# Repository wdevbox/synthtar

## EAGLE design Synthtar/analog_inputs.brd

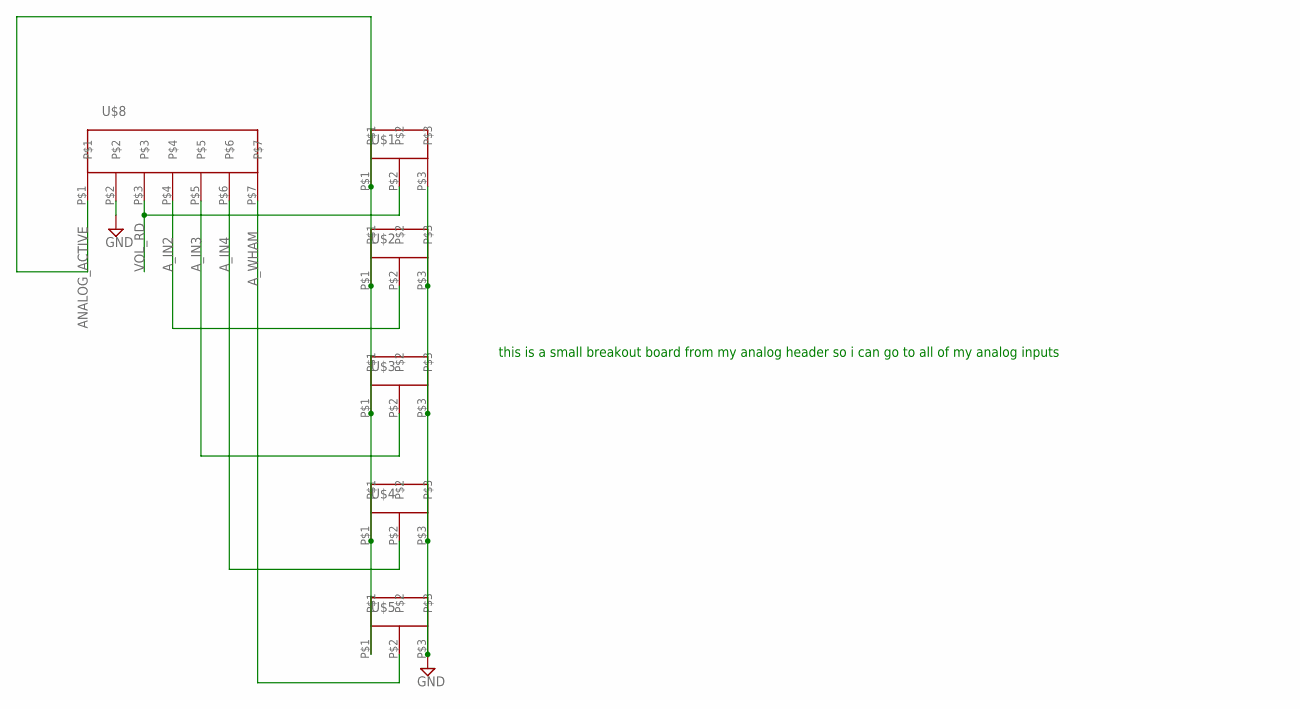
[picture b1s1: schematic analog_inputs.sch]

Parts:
U$1, U$2, U$3, U$4, U$5: 3-PIN-HEADER
U$8: 7-PIN-HEADER

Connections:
ANALOG_ACTIVE: U$1.P$1, U$2.P$1, U$3.P$1, U$4.P$1, U$5.P$1, U$8.P$1
A_IN2: U$2.P$2, U$8.P$4
A_IN3: U$3.P$2, U$8.P$5
A_IN4: U$4.P$2, U$8.P$6
A_WHAM: U$5.P$2, U$8.P$7
GND: U$1.P$3, U$2.P$3, U$3.P$3, U$4.P$3, U$5.P$3, U$8.P$2
VOL_RD: U$1.P$2, U$8.P$3

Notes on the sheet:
this is a small breakout board from my analog header so i can go to all of my analog inputs

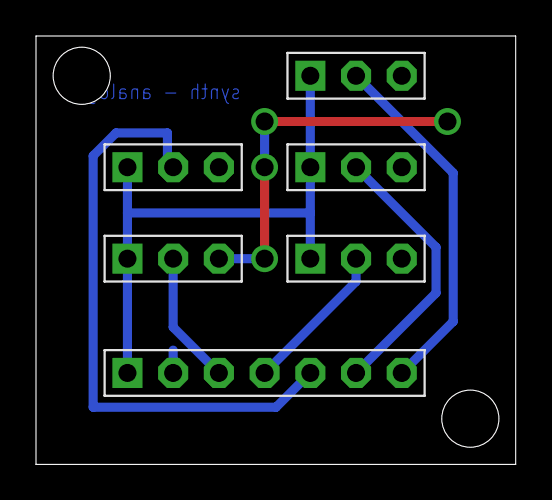
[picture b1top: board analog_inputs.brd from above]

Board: 2 copper layers, 26.7 x 23.8 mm, 6 parts (0 on the bottom side), 7 nets.

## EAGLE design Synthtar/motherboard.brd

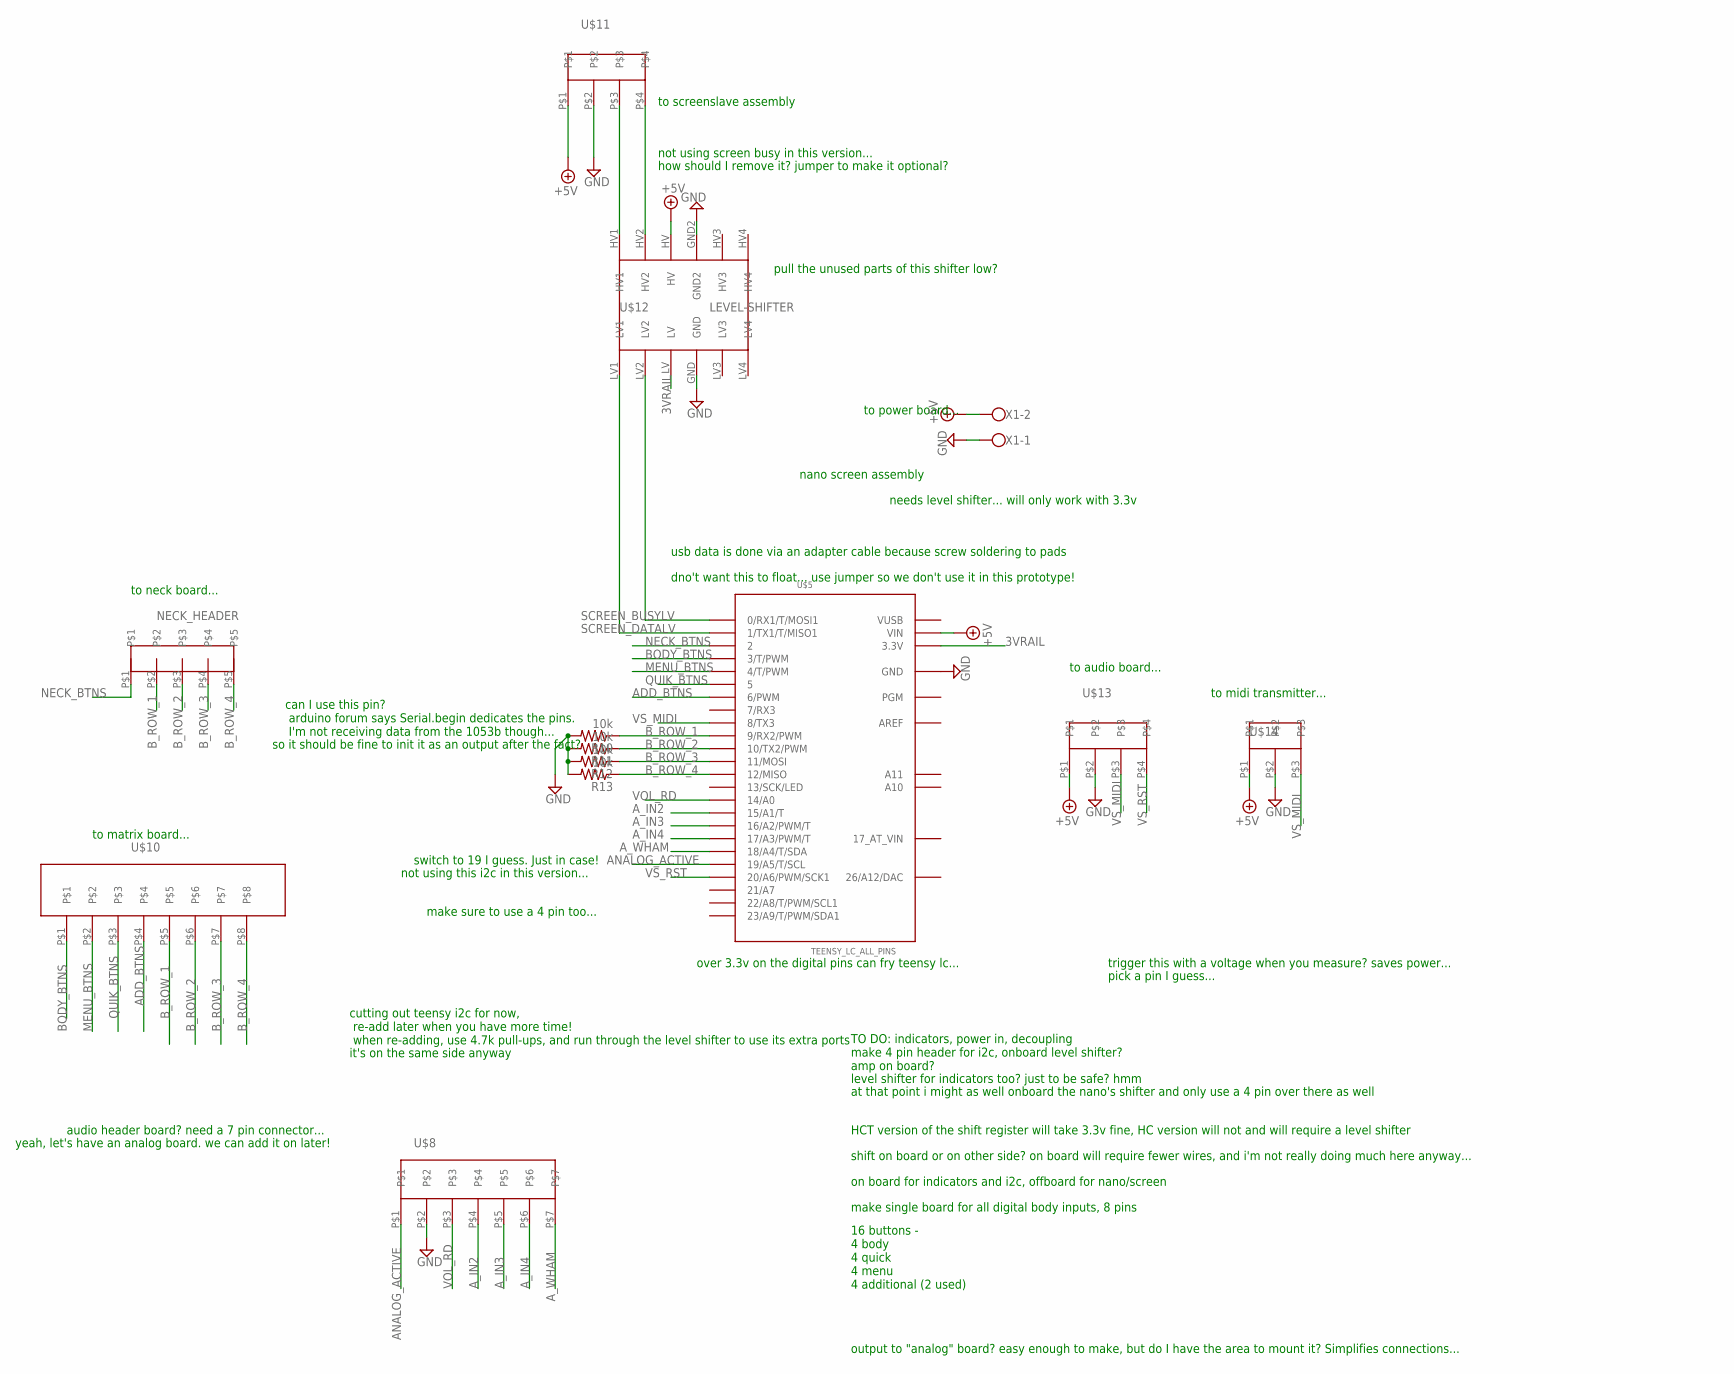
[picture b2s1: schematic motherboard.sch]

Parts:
NECK_HEADER: 5-PIN-HEADER
R10, R11, R12, R13: 10k; 0204/7
U$5: TEENSY_LC_ALL_PINS; TEENSY_3.0-3.2&LC_ALL_PINS
U$8: 7-PIN-HEADER
U$10: 8-PIN-HEADER
U$11, U$13: 4-PIN-HEADER
U$12: LEVEL-SHIFTER
U$14: 3-PIN-HEADER
X1: W237-102

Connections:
3VRAIL: U$5.3.3V, U$5.3.3V1 (3.3V), U$12.LV
26/A12/DAC: U$5.RESET/DAC (26/A12/DAC)
+5V: U$5.VIN, U$11.P$1, U$12.HV, U$13.P$1, U$14.P$1, X1.2
ADD_BTNS: U$5.6 (6/PWM), U$10.P$4
ANALOG_ACTIVE: U$5.19/A5 (19/A5/T/SCL), U$8.P$1
AREF: U$5.AREF
A_IN2: U$5.15/A1 (15/A1/T), U$8.P$4
A_IN3: U$5.16/A2 (16/A2/PWM/T), U$8.P$5
A_IN4: U$5.17/A3 (17/A3/PWM/T), U$8.P$6
A_WHAM: U$5.18/A4 (18/A4/T/SDA), U$8.P$7
BODY_BTNS: U$5.3 (3/T/PWM), U$10.P$1
B_ROW_1: NECK_HEADER.P$2, R10.1, U$5.9 (9/RX2/PWM), U$10.P$5
B_ROW_2: NECK_HEADER.P$3, R11.1, U$5.10 (10/TX2/PWM), U$10.P$6
B_ROW_3: NECK_HEADER.P$4, R12.1, U$5.11 (11/MOSI), U$10.P$7
B_ROW_4: NECK_HEADER.P$5, R13.1, U$5.12 (12/MISO), U$10.P$8
GND: R10.2, R11.2, R12.2, R13.2, U$5.AGND (GND), U$5.GND, U$5.GND1 (GND), U$8.P$2, U$11.P$2, U$12.GND, U$12.GND2, U$13.P$2, U$14.P$2, X1.1
MENU_BTNS: U$5.4 (4/T/PWM), U$10.P$2
unnamed: U$11.P$3, U$12.HV1
unnamed: U$11.P$4, U$12.HV2
NECK_BTNS: NECK_HEADER.P$1, U$5.2
QUIK_BTNS: U$5.5, U$10.P$3
SCREEN_BUSYLV: U$5.0 (0/RX1/T/MOSI1), U$12.LV2
SCREEN_DATALV: U$5.1 (1/TX1/T/MISO1), U$12.LV1
VOL_RD: U$5.14/A0, U$8.P$3
VS_MIDI: U$5.8 (8/TX3), U$13.P$3, U$14.P$3
VS_RST: U$5.20/A6 (20/A6/PWM/SCK1), U$13.P$4
VUSB: U$5.VUSB

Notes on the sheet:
over 3.3v on the digital pins can fry teensy lc...
nano screen assembly
TO DO: indicators, power in, decoupling make 4 pin header for i2c, onboard level shifter? amp on board?
level shifter for indicators too? just to be safe? hmm
at that point i might as well onboard the nano's shifter and only use a 4 pin over there as well
HCT version of the shift register will take 3.3v fine, HC version will not and will require a level shifter
shift on board or on other side? on board will require fewer wires, and i'm not really doing much here anyway...
needs level shifter... will only work with 3.3v
on board for indicators and i2c, offboard for nano/screen
make single board for all digital body inputs, 8 pins
16 buttons - 4 body 4 quick 4 menu 4 additional (2 used)
output to "analog" board? easy enough to make, but do I have the area to mount it? Simplifies connections...
to matrix board...
to neck board...
to power board...
to audio board...
to midi transmitter...
usb data is done via an adapter cable because screw soldering to pads
to screenslave assembly
not using screen busy in this version...
how should I remove it? jumper to make it optional?
pull the unused parts of this shifter low?
dno't want this to float... use jumper so we don't use it in this prototype!
not using this i2c in this version...
audio header board? need a 7 pin connector...
yeah, let's have an analog board. we can add it on later!
trigger this with a voltage when you measure? saves power...
pick a pin I guess...
can I use this pin? arduino forum says Serial.begin dedicates the pins. I'm not receiving data from the 1053b though...
so it should be fine to init it as an output after the fact?
switch to 19 I guess. Just in case!
cutting out teensy i2c for now, re-add later when you have more time! when re-adding, use 4.7k pull-ups, and run through the level shifter to use its extra ports
it's on the same side anyway
make sure to use a 4 pin too...

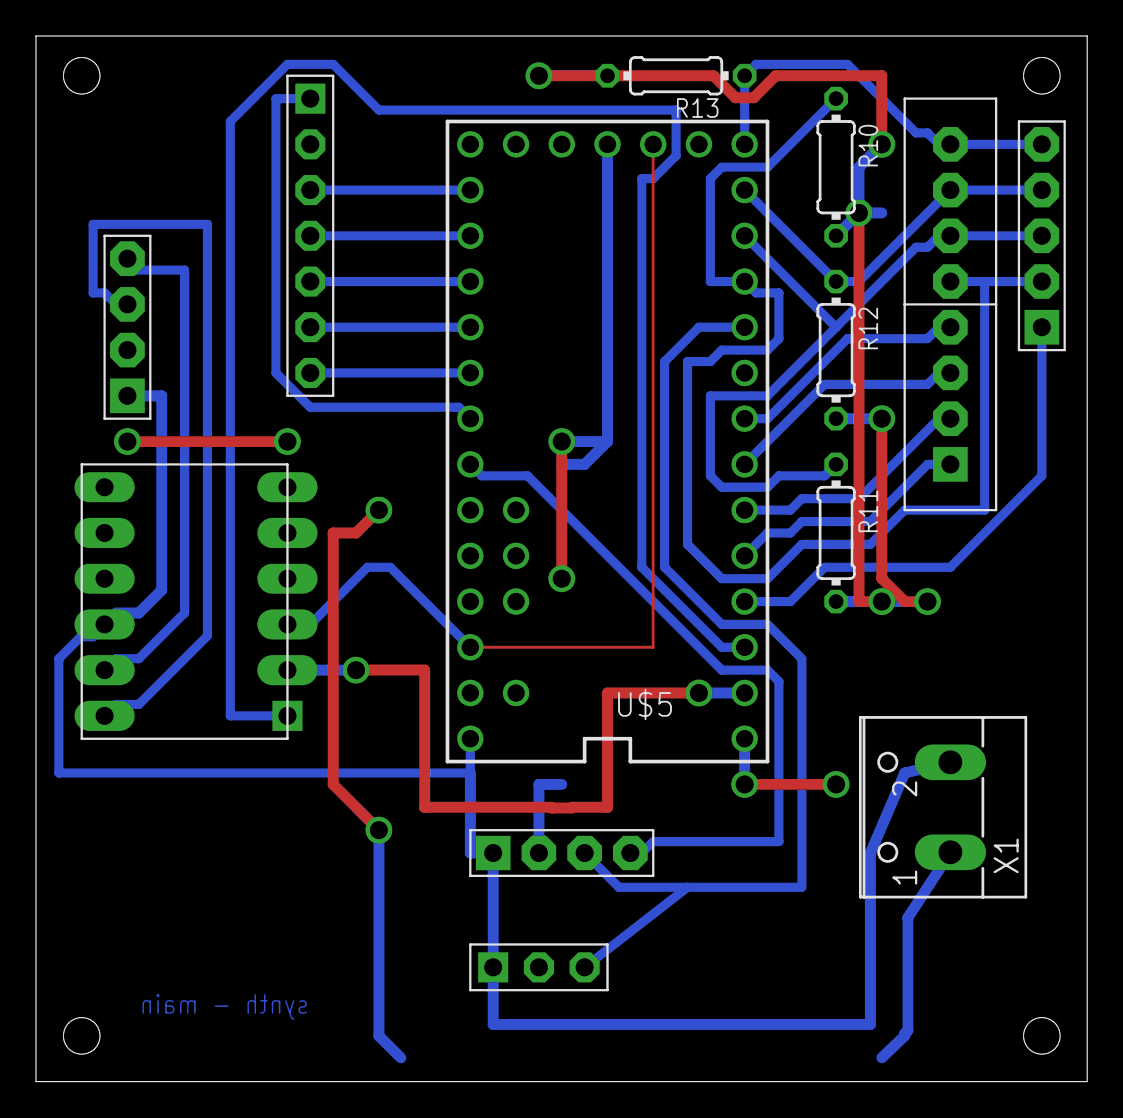
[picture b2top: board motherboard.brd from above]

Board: 2 copper layers, 58.4 x 58.1 mm, 13 parts (0 on the bottom side), 24 nets.

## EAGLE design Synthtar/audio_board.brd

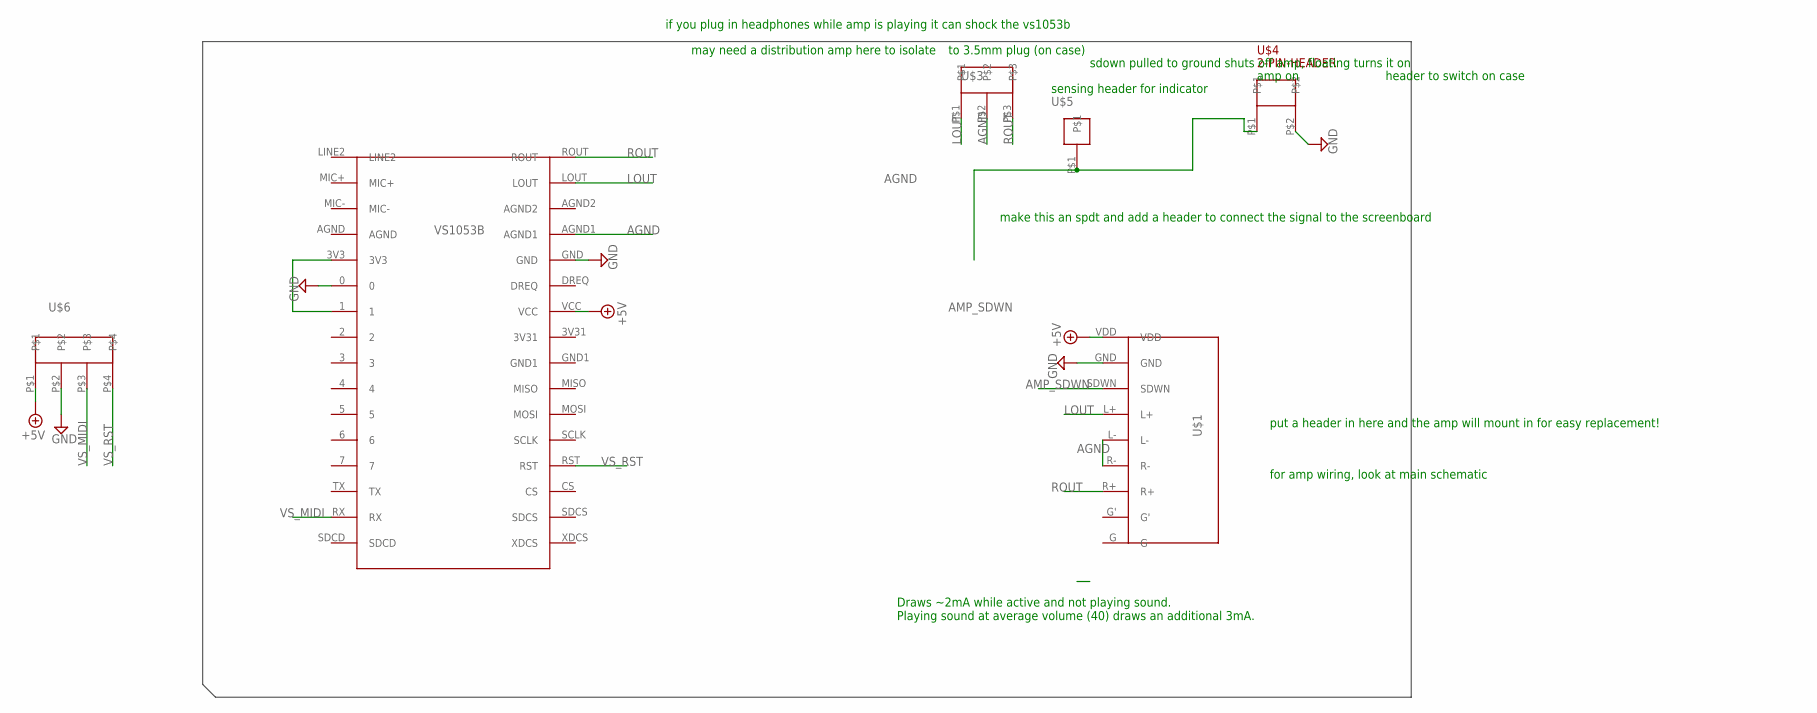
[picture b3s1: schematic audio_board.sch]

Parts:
U$1: AUDIOAMP
U$3: 3-PIN-HEADER
U$4: 2-PIN-HEADER
U$5: 1-PIN-HEADER
U$6: 4-PIN-HEADER
VS1053B: VS1053B

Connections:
+5V: U$1.VDD, U$6.P$1, VS1053B.VCC
AGND: U$1.L-, U$1.R-, U$3.P$2, VS1053B.AGND1
AMP_SDWN: U$1.SDWN, U$4.P$1, U$5.P$1
GND: U$1.GND, U$4.P$2, U$6.P$2, VS1053B.0, VS1053B.GND
LOUT: U$1.L+, U$3.P$1, VS1053B.LOUT
unnamed: VS1053B.1, VS1053B.3V3
ROUT: U$1.R+, U$3.P$3, VS1053B.ROUT
VS_MIDI: U$6.P$3, VS1053B.RX
VS_RST: U$6.P$4, VS1053B.RST

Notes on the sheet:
amp on
sdown pulled to ground shuts off amp, floating turns it on
Draws ~2mA while active and not playing sound. Playing sound at average volume (40) draws an additional 3mA.
may need a distribution amp here to isolate
if you plug in headphones while amp is playing it can shock the vs1053b
make this an spdt and add a header to connect the signal to the screenboard
to 3.5mm plug (on case)
header to switch on case
sensing header for indicator
put a header in here and the amp will mount in for easy replacement!
for amp wiring, look at main schematic

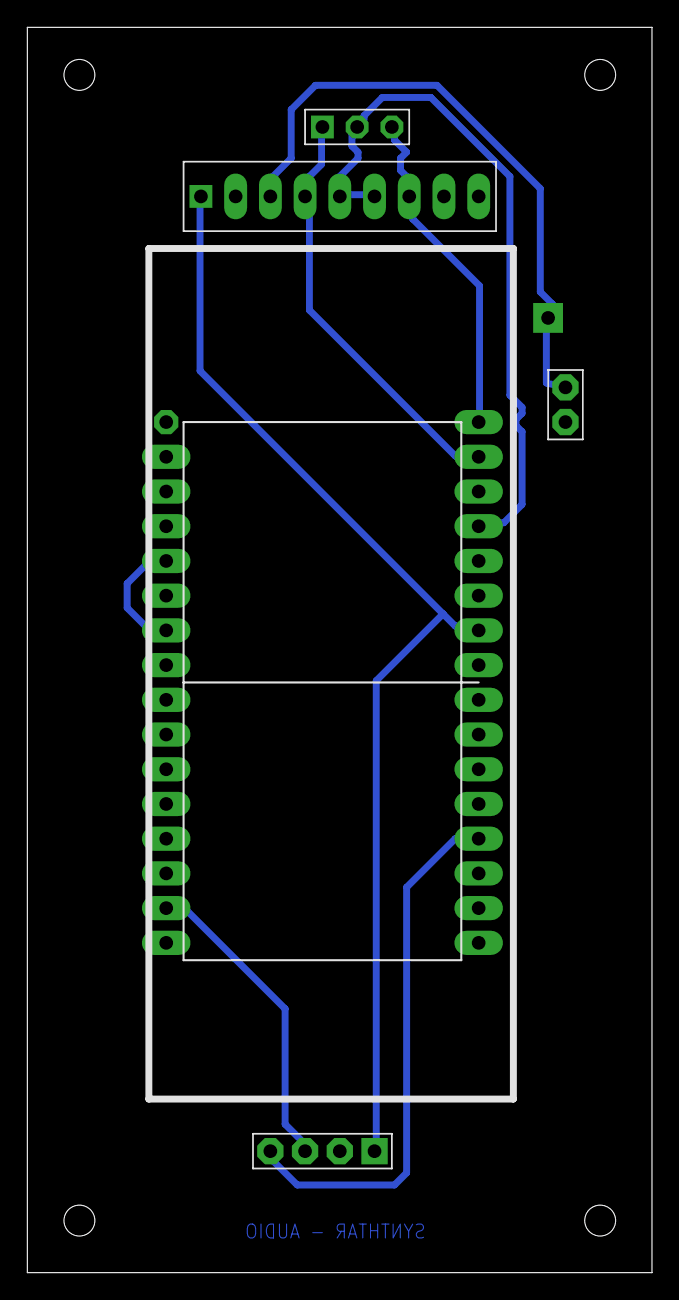
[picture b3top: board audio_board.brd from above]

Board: 2 copper layers, 45.7 x 91.1 mm, 6 parts (0 on the bottom side), 9 nets.

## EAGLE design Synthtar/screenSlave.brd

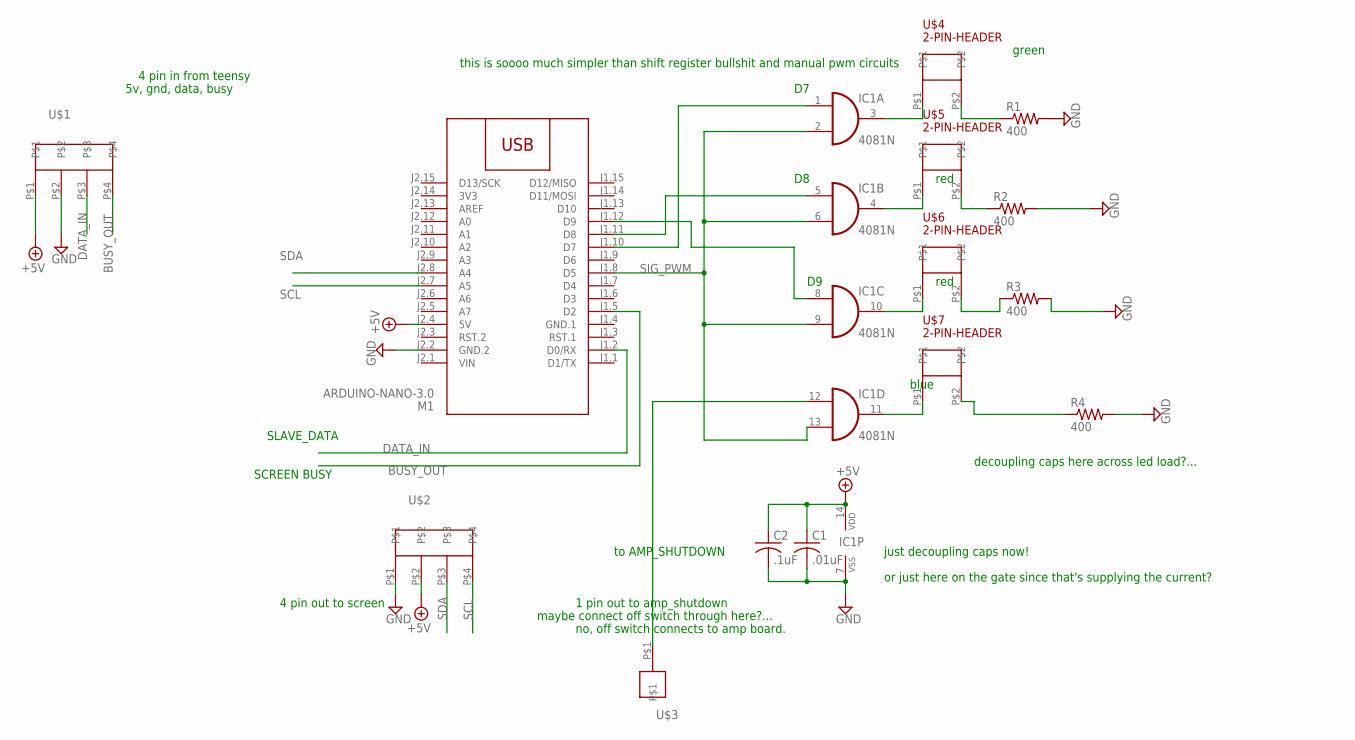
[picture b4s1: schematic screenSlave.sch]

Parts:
C1: .01uF; C025-024X044
C2: .1uF; C025-024X044
IC1: 4081N; DIL14
M1: ARDUINO-NANO-3.0
R1, R2, R3, R4: 400; 0204/7
U$1, U$2: 4-PIN-HEADER
U$3: 1-PIN-HEADER
U$4, U$5, U$6, U$7: 2-PIN-HEADER

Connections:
3V3: M1.J2.14 (3V3)
+5V: C1.1, C2.1, IC1.14 (VDD), M1.J2.4 (5V), U$1.P$1, U$2.P$2
BUSY_OUT: M1.J1.5 (D2), U$1.P$4
DATA_IN: M1.J1.2 (D0/RX), U$1.P$3
GND: C1.2, C2.2, IC1.7 (VSS), M1.J2.2 (GND.2), R1.2, R2.2, R3.2, R4.2, U$1.P$2, U$2.P$1
GND.1: M1.J1.4 (GND.1)
unnamed: IC1.12 (I0), U$3.P$1
unnamed: IC1.11 (O), U$7.P$1
unnamed: IC1.3 (O), U$4.P$1
unnamed: R1.1, U$4.P$2
unnamed: IC1.4 (O), U$5.P$1
unnamed: IC1.10 (O), U$6.P$1
unnamed: R3.1, U$6.P$2
unnamed: IC1.1 (I0), M1.J1.10 (D7)
unnamed: R2.1, U$5.P$2
unnamed: IC1.5 (I0), M1.J1.11 (D8)
unnamed: IC1.8 (I0), M1.J1.12 (D9)
unnamed: R4.1, U$7.P$2
SCL: M1.J2.7 (A5), U$2.P$4
SDA: M1.J2.8 (A4), U$2.P$3
SIG_PWM: IC1.2 (I1), IC1.6 (I1), IC1.9 (I1), IC1.13 (I1), M1.J1.8 (D5)
VIN: M1.J2.1 (VIN)

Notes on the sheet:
blue
red
green
to AMP_SHUTDOWN
SLAVE_DATA
SCREEN BUSY
4 pin in from teensy
4 pin out to screen
1 pin out to amp_shutdown
5v, gnd, data, busy
maybe connect off switch through here?...
this is soooo much simpler than shift register bullshit and manual pwm circuits
just decoupling caps now!
decoupling caps here across led load?...
or just here on the gate since that's supplying the current?
no, off switch connects to amp board.

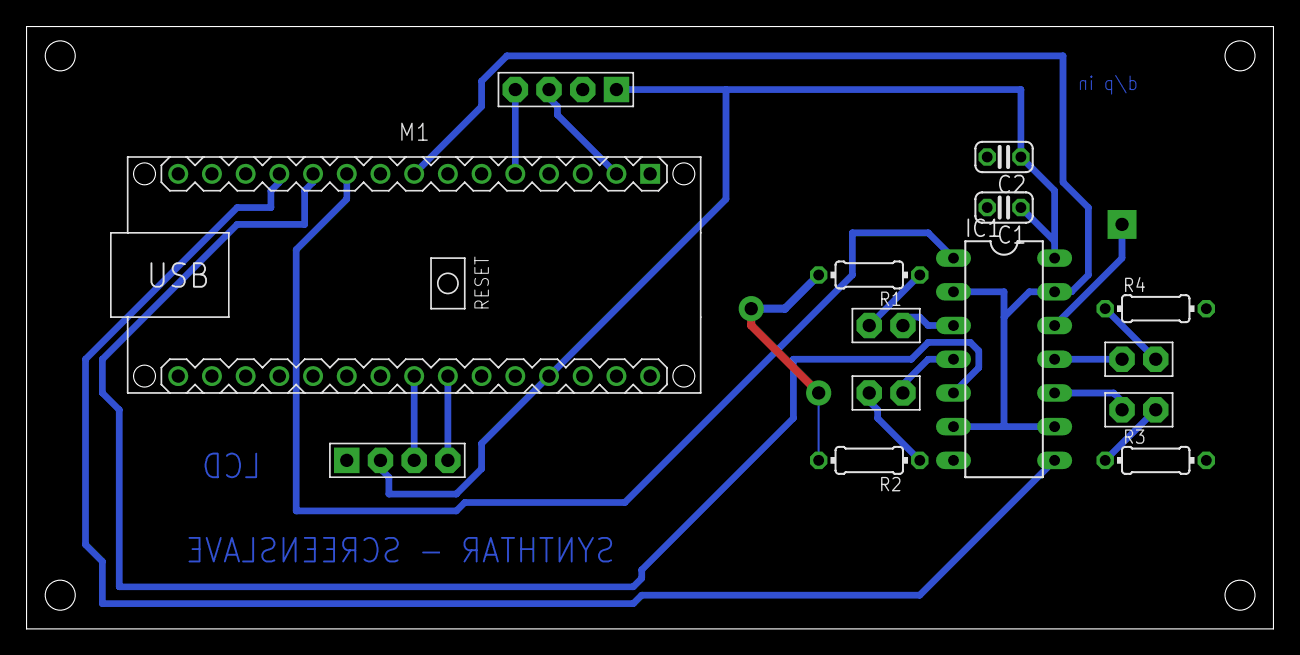
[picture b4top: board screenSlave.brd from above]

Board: 2 copper layers, 94.0 x 45.4 mm, 15 parts (0 on the bottom side), 19 nets.

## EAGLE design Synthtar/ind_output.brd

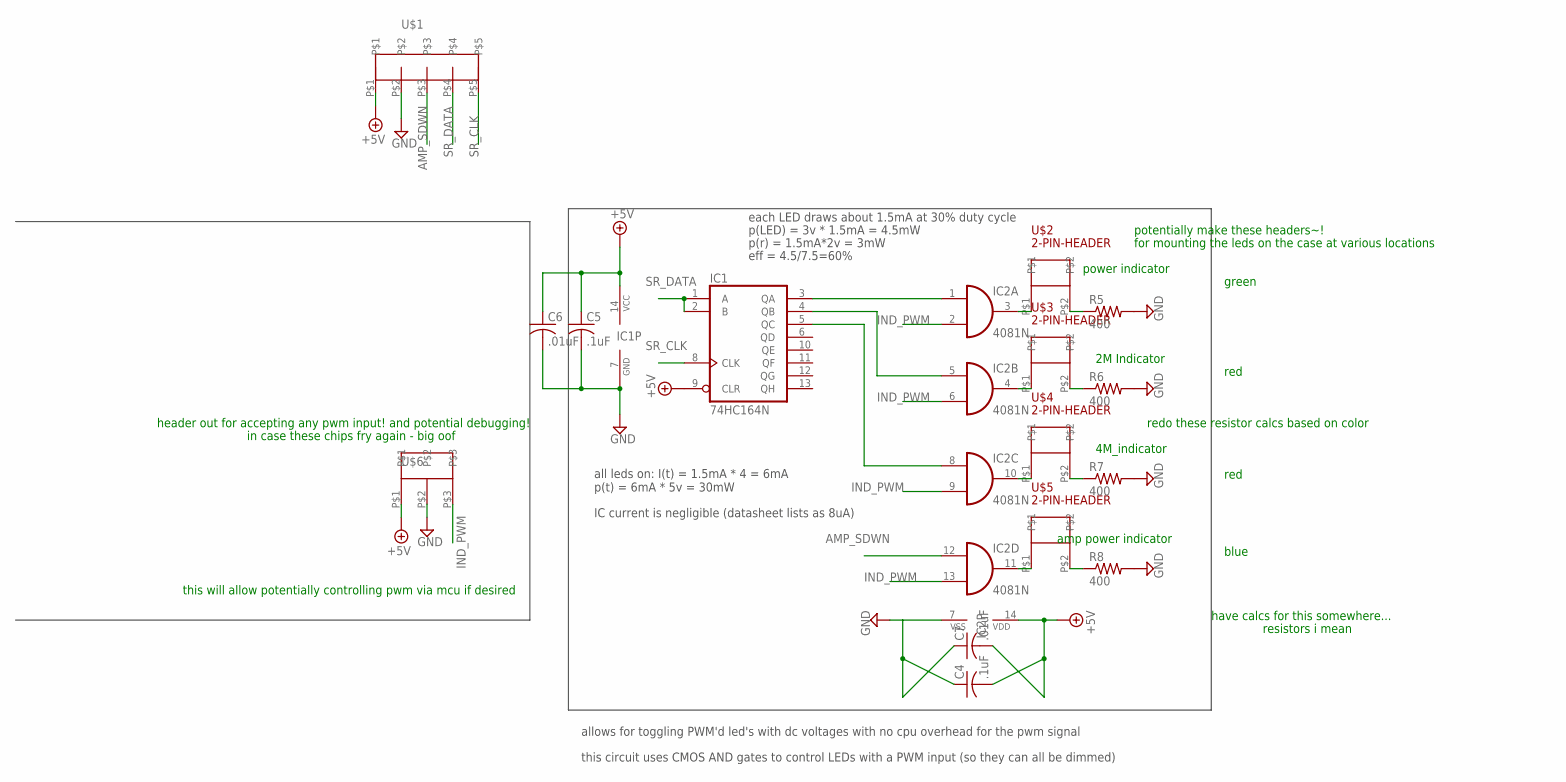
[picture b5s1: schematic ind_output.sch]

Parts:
C4, C5: .1uF; C025-030X050
C6, C7: .01uF; C025-030X050
IC1: 74HC164N; DIL14
IC2: 4081N; DIL14
R5, R6, R7, R8: 400; 0204/7
U$1: 5-PIN-HEADER
U$2, U$3, U$4, U$5: 2-PIN-HEADER
U$6: 3-PIN-HEADER

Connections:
+5V: C4.2, C5.1, C6.1, C7.2, IC1.9 (CLR), IC1.14 (VCC), IC2.14 (VDD), U$1.P$1, U$6.P$1
AMP_SDWN: IC2.12 (I0), U$1.P$3
GND: C4.1, C5.2, C6.2, C7.1, IC1.7 (GND), IC2.7 (VSS), R5.2, R6.2, R7.2, R8.2, U$1.P$2, U$6.P$2
IND_PWM: IC2.2 (I1), IC2.6 (I1), IC2.9 (I1), IC2.13 (I1), U$6.P$3
unnamed: IC1.3 (QA), IC2.1 (I0)
unnamed: IC1.4 (QB), IC2.5 (I0)
unnamed: IC2.3 (O), U$2.P$1
unnamed: IC1.5 (QC), IC2.8 (I0)
unnamed: R5.1, U$2.P$2
unnamed: IC2.4 (O), U$3.P$1
unnamed: R6.1, U$3.P$2
unnamed: IC2.10 (O), U$4.P$1
unnamed: R7.1, U$4.P$2
unnamed: IC2.11 (O), U$5.P$1
unnamed: R8.1, U$5.P$2
SR_CLK: IC1.8 (CLK), U$1.P$5
SR_DATA: IC1.1 (A), IC1.2 (B), U$1.P$4

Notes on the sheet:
amp power indicator
2M Indicator
4M_indicator
power indicator
this circuit uses CMOS AND gates to control LEDs with a PWM input (so they can all be dimmed)
allows for toggling PWM'd led's with dc voltages with no cpu overhead for the pwm signal
each LED draws about 1.5mA at 30% duty cycle
p(LED) = 3v * 1.5mA = 4.5mW
p(r) = 1.5mA*2v = 3mW
eff = 4.5/7.5=60%
all leds on: I(t) = 1.5mA * 4 = 6mA p(t) = 6mA * 5v = 30mW
IC current is negligible (datasheet lists as 8uA)
potentially make these headers~!
for mounting the leds on the case at various locations
redo these resistor calcs based on color
green
blue
red
have calcs for this somewhere...
resistors i mean
header out for accepting any pwm input! and potential debugging!
in case these chips fry again - big oof
this will allow potentially controlling pwm via mcu if desired

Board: 2 copper layers, 16 parts (0 on the bottom side), 17 nets, no tracks yet.

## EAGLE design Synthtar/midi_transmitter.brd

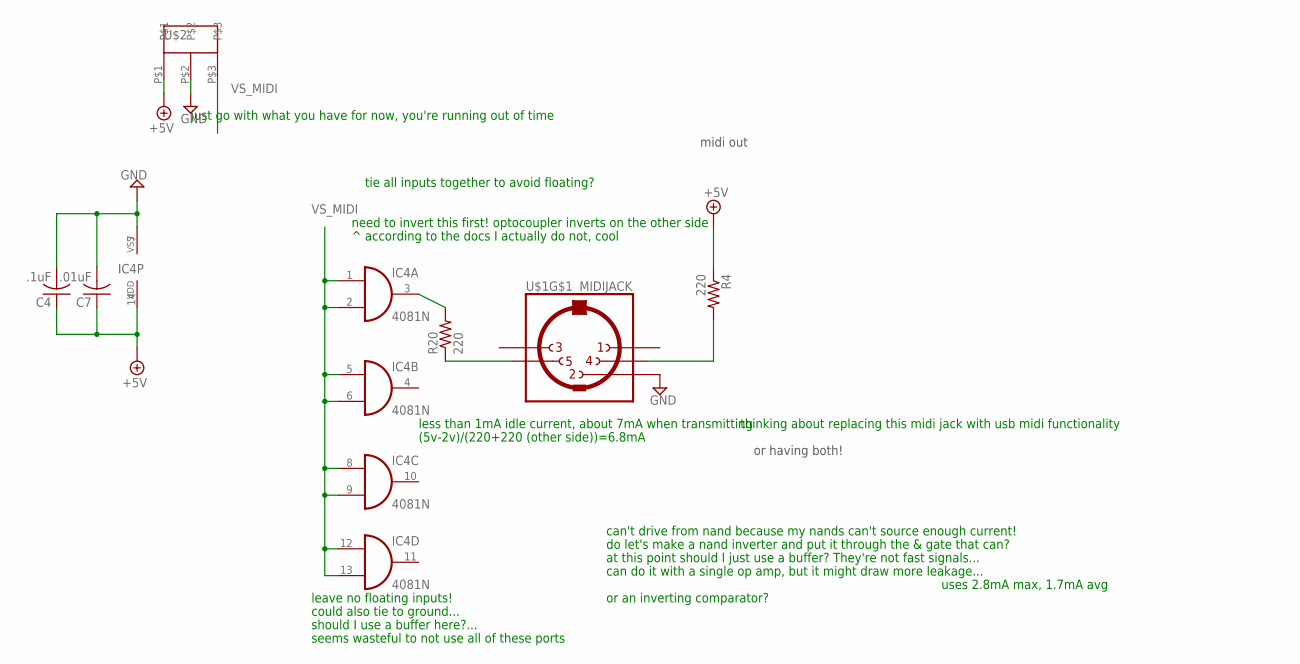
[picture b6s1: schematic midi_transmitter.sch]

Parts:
C4: .1uF; C025-030X050
C7: .01uF; C025-030X050
IC4: 4081N; DIL14
R4, R20: 220; 0204/7
U$1: MIDIJACK; CP-2350
U$2: 3-PIN-HEADER

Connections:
+5V: C4.1, C7.1, IC4.14 (VDD), R4.1, U$2.P$1
GND: C4.2, C7.2, IC4.7 (VSS), U$1.2, U$2.P$2
unnamed: IC4.3 (O), R20.2
unnamed: R4.2, U$1.4
unnamed: R20.1, U$1.5
VS_MIDI: IC4.1 (I0), IC4.2 (I1), IC4.5 (I0), IC4.6 (I1), IC4.8 (I0), IC4.9 (I1), IC4.12 (I0), IC4.13 (I1), U$2.P$3

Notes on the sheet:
midi out
thinking about replacing this midi jack with usb midi functionality
or having both!
need to invert this first! optocoupler inverts on the other side
tie all inputs together to avoid floating?
can't drive from nand because my nands can't source enough current!
do let's make a nand inverter and put it through the & gate that can?
at this point should I just use a buffer? They're not fast signals...
can do it with a single op amp, but it might draw more leakage...
or an inverting comparator?
uses 2.8mA max, 1.7mA avg
just go with what you have for now, you're running out of time
^ according to the docs I actually do not, cool
less than 1mA idle current, about 7mA when transmitting
(5v-2v)/(220+220 (other side))=6.8mA
leave no floating inputs!
could also tie to ground...
should I use a buffer here?...
seems wasteful to not use all of these ports

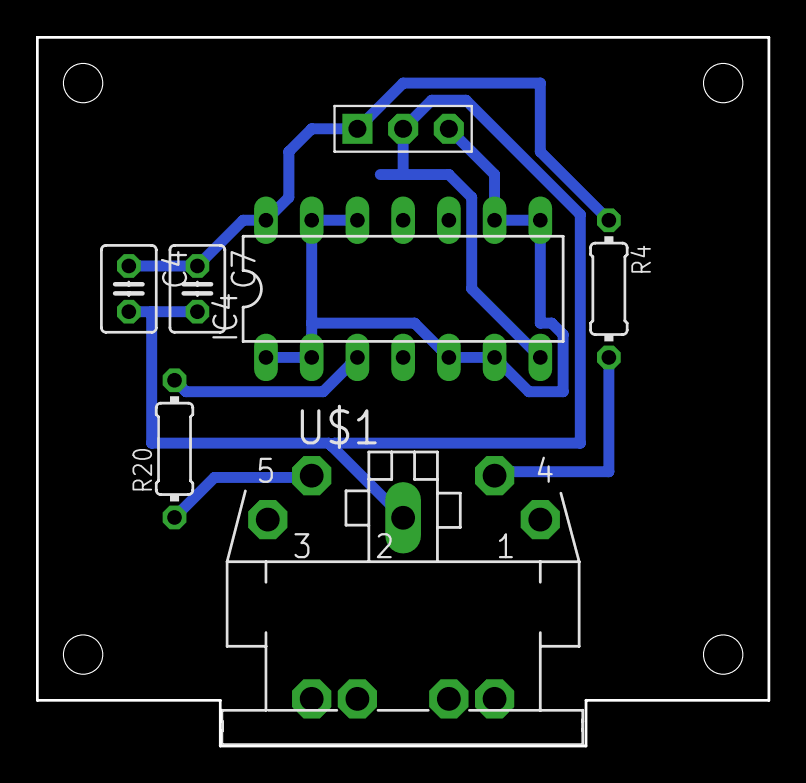
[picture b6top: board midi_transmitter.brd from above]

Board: 2 copper layers, 40.6 x 39.4 mm, 7 parts (0 on the bottom side), 6 nets.

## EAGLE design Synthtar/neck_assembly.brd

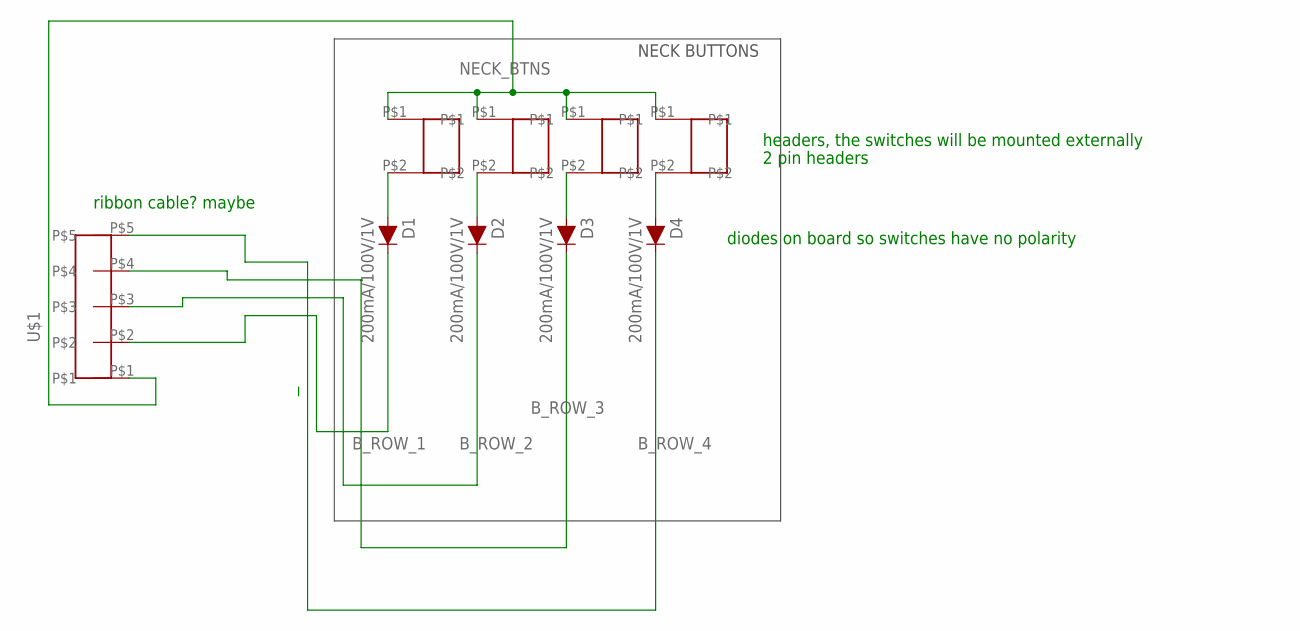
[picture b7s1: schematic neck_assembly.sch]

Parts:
B1, B2, B3, B4: 2-PIN-HEADER
D1, D2, D3, D4: 200mA/100V/1V; DIODE-1N4148
U$1: 5-PIN-HEADER

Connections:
B_ROW_1: D1.C, U$1.P$2
B_ROW_2: D2.C, U$1.P$3
B_ROW_3: D3.C, U$1.P$4
B_ROW_4: D4.C, U$1.P$5
unnamed: B1.P$2, D1.A
unnamed: B2.P$2, D2.A
unnamed: B3.P$2, D3.A
unnamed: B4.P$2, D4.A
NECK_BTNS: B1.P$1, B2.P$1, B3.P$1, B4.P$1, U$1.P$1

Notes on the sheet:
NECK BUTTONS
headers, the switches will be mounted externally
2 pin headers
diodes on board so switches have no polarity
ribbon cable? maybe

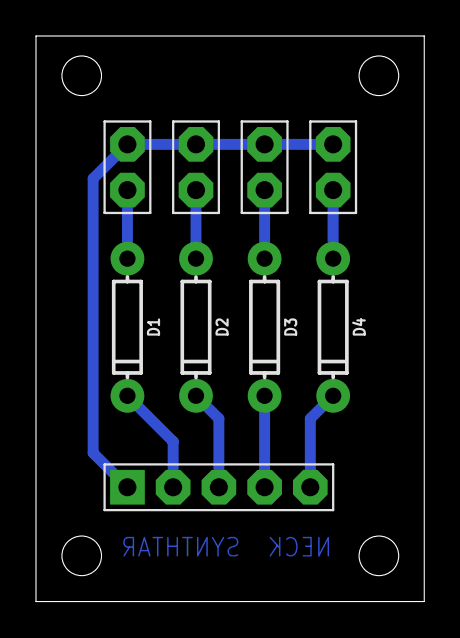
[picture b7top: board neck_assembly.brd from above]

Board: 2 copper layers, 21.6 x 31.4 mm, 9 parts (0 on the bottom side), 9 nets.

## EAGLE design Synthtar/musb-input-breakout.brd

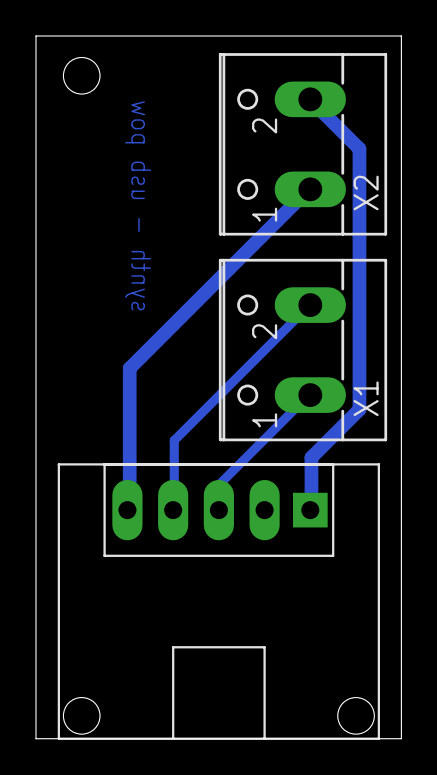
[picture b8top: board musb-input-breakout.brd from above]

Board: 2 copper layers, 20.3 x 39.0 mm, 3 parts (0 on the bottom side), 4 nets.

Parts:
U$1: MICRO-USB
X1, X2: W237-102

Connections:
unnamed: U$1.GND, X2.2
unnamed: U$1.5V, X2.1
unnamed: U$1.D+, X1.1
unnamed: U$1.D-, X1.2

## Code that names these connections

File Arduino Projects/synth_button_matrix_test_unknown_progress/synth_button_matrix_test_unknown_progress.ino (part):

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#define ROW_4 12
#define A_ACTIVE 19
#define A_VOL 14
#define A_IN2 15
#define A_IN3 16
#define A_IN4 17
#define A_WHAM 18
//MIDI DEFINITIONS
#define DEFAULT_ROOT 52 //default root note
#define DEFAULT_INST 31 //default instrument
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 // pinMode(18, OUTPUT); digitalWrite(18, 0); //set the output high to turn on the AND gate and see if the 3.3v logic will trigger it. This can be thought of as power indicator or something
  pinMode(A_ACTIVE, OUTPUT); digitalWrite(A_ACTIVE, LOW);
  pinMode(A_VOL, INPUT);
  pinMode(A_IN2, INPUT);
  pinMode(A_IN3, INPUT);
  pinMode(A_IN4, INPUT); //set as inputs so they don't put a voltage across there...
  pinMode(A_WHAM, INPUT); //is there a different version in the github...?
  }
void midiInitStuff(){
    midiSetChannelBank(0, VS1053_BANK_MELODY); //set instrument bank to melody
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
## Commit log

2019-03-16 Create synth_button_matrix_test.ino
    Sort of works, when pressing buttons in col1, a: strings don't change note (they do if you press them while the string is playing?) b: one of the buttons reads as row1 for col2 as well. no idea why. 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
2019-03-16 Update synth_button_matrix_test.ino
    fixed changing not working when not pressed, some issue with the for each loop, didn't like it for some reason. changed it to a dumb for loop and now it works properly
    fixed button reading weird, it was either electrical noise or some capacitance/the diode not being able to charge fast enough. added a small delay before the first read of the next column and the iss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
    still need to fix the "losing notes" bug when you switch root while you're playing a chord, comments are in there
2019-04-20 Schematics upload
    In the process of adding an additional circuit for a nano to control the LCD to save processing time from teensy, because I got a 16x2 LCD from the lab and it doesn't have SPI, only parallel.
    Country boys make do
2019-04-20 excel sheets
    added some additional docs
2019-04-20 more uploads
    more recent files. code improvements
2019-04-22 Board building
    started migrating overall schematic into individual boards
2019-04-22 indicator assembly
    finished indicator board
2019-04-22 Whammy Bar!
    Finally added whammy bar, an old ps3 analog stick
2019-04-23 midi transmitter + lots of others
    midi transmitter board, main motherboard with headers to connect to everything else
2019-04-24 joystick breakout for whammy
    created joystick breakout and added some more headers/notes to the mainboard
2019-04-25 indicator update
    honestly don't remmember what i changed, looks like added a header maybe?
2019-05-03 making boards and taking care of business
    honestly haven't made a commit in so fucking long
2019-05-06 big changes
    changed a ton
2019-05-06 changed a_active to pin 19
    so it's not on a serial line. arduino forums said after Serial.begin() it becomes unpredictable
2019-05-06 finished motherboard
    enough jumpers to fill a bad third eye blind playlist
    started making musb breakout for connecting power and data independently
2019-05-09 so fucking much
    a
2019-05-16 misc changes
    misc updates while doing documentation
2019-05-16 added code for screenslave and main teensy
    also fixed some resistor values in overall schem
2019-05-16 deleted some comments
    deleted comments in midi trasmitter
2019-05-16 Update Users Manual - Synthtar.docx
    updated user's manual (still needs work)
2019-05-16 Update Users Manual - Synthtar.docx
    minor edits (still needs work, but i'm too tired)
2019-05-16 Update Users Manual - Synthtar.docx
    updated - calling it good
2019-05-16 Update Users Manual - Synthtar.docx
    minor edits

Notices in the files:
parts and their libraries:
SparkFun-DiscreteSemi: Licensing: Creative Commons ShareAlike 4.0 International - https://creativecommons.org/licenses/by-sa/4.0
diy-modules: Released under the Creative Commons Attribution 4.0 International License: http://creativecommons.org/licenses/by/4.0
